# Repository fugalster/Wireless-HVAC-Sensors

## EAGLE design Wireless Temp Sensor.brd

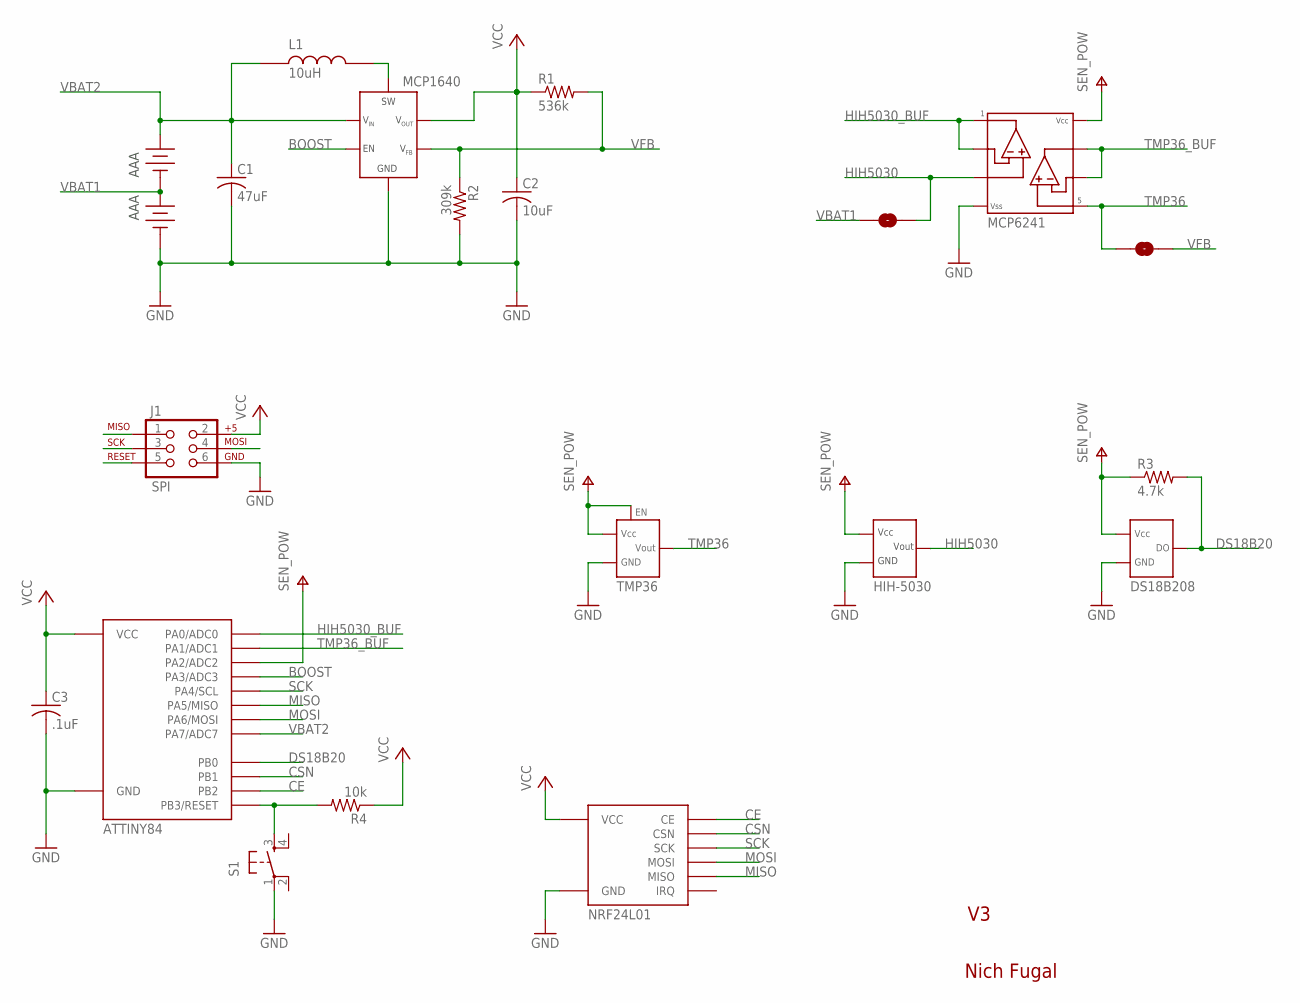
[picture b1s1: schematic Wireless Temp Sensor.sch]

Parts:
C1: 47uF; C0805
C2: 10uF; C0805
C3: .1uF; C0805
J1: SPI; 2X3
R1: 536k; M0805
R2: 309k; M0805
R3: 4.7k; M0805
R4: 10k; M0805
S1: TAC_SWITCHPTH; TACTILE-PTH
SJ1, SJ2: SOLDERJUMPER-OLDNO; SJ_2S-NO
U1: TMP36; SOT-23-5
U$1: MCP1640; SOT-23
U$2: 10uH; SD3114
U$3, U$8: AAA; BK-82_MPD
U$4: ATTINY84; 14-DIP
U$5: NRF24L01
U$6: DS18B208; 8-MSOP
U$7: HIH-5030
U$9: MCP6241; 8-SOIC

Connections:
BOOST: U$1.3 (EN), U$4.P$10 (PA3/ADC3)
CE: U$4.P$5 (PB2), U$5.P$3 (CE)
CSN: U$4.P$3 (PB1), U$5.P$4 (CSN)
DS18B20: R3.2, U$4.P$2 (PB0), U$6.P$1 (DO)
GND: C1.2, C2.2, C3.2, J1.6, R2.2, S1.1, U1.5 (GND), U$1.2 (GND), U$4.P$14 (GND), U$5.P$1 (GND), U$6.P$4 (GND), U$7.GND, U$8.P$3 (-), U$8.P$4 (-), U$9.P$4
HIH5030: SJ1.1, U$7.OUT, U$9.P$3
HIH5030_BUF: U$4.P$13 (PA0/ADC0), U$9.P$1, U$9.P$2
MISO: J1.1, U$4.P$8 (PA5/MISO), U$5.P$7 (MISO)
MOSI: J1.4, U$4.P$7 (PA6/MOSI), U$5.P$6 (MOSI)
unnamed: U$1.1 (SW), U$2.P$2
RESET: J1.5, R4.2, S1.3, U$4.P$4 (PB3/RESET)
SCK: J1.3, U$4.P$9 (PA4/SCL), U$5.P$5 (SCK)
SEN_POW: R3.1, U1.2 (VCC), U1.4 (EN), U$4.P$11 (PA2/ADC2), U$6.P$8 (VCC), U$7.VCC, U$9.P$8
TMP36: SJ2.1, U1.1 (VOUT), U$9.P$5
TMP36_BUF: U$4.P$12 (PA1/ADC1), U$9.P$6, U$9.P$7
VBAT1: SJ1.2, U$3.P$3 (-), U$3.P$4 (-), U$8.P$1 (+), U$8.P$2 (+)
VBAT2: C1.1, U$1.6 (VIN), U$2.P$1, U$3.P$1 (+), U$3.P$2 (+), U$4.P$6 (PA7/ADC7)
VCC: C2.1, C3.1, J1.2, R1.1, R4.1, U$1.5 (VOUT), U$4.P$1 (VCC), U$5.P$2 (VCC)
VFB: R1.2, R2.1, SJ2.2, U$1.4 (VFB)

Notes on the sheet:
AAA
10uH
Nich Fugal

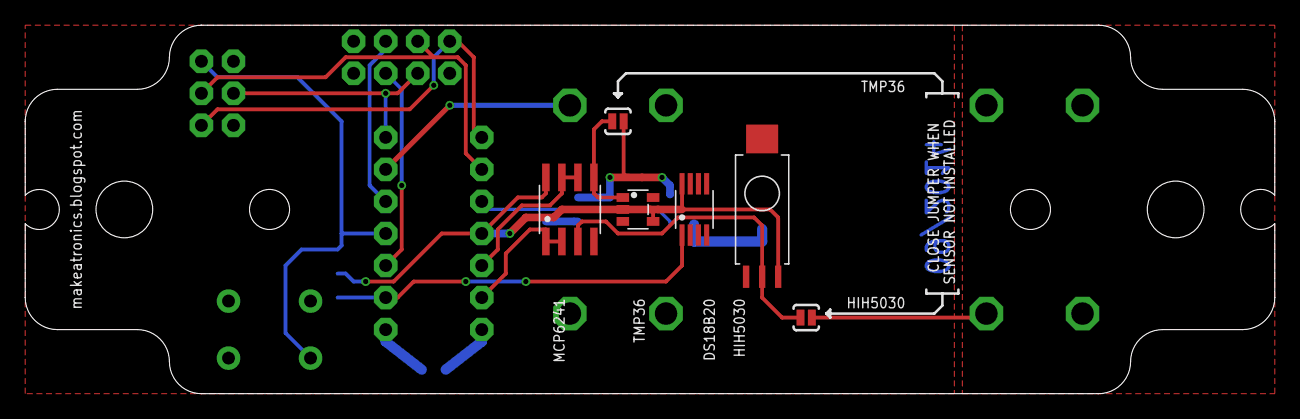
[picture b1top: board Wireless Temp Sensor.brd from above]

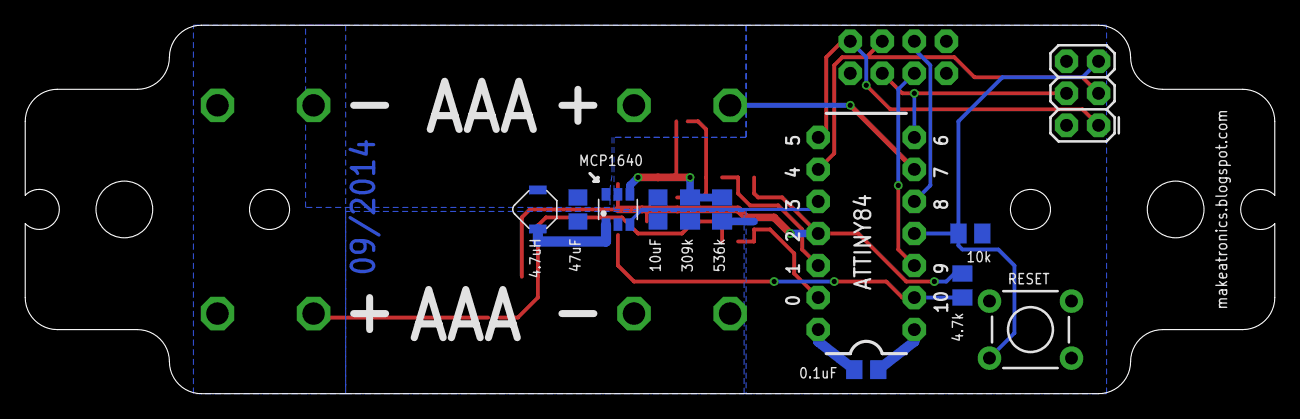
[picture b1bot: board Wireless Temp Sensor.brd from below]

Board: 2 copper layers, 99.1 x 29.2 mm, 21 parts (15 on the bottom side), 19 nets.

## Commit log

2014-09-14 :space_invader: Added .gitattributes
2014-09-14 Added design files
2014-09-23 V3.1
    Minor modifications to copper fill and battery terminal spacing.
2014-09-23 Updated board image to V3.1

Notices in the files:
parts and their libraries:
sparkfun: Licensing: CC v3.0 Share-Alike You are welcome to use this library for commercial purposes.
